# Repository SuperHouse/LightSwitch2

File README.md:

Home Automation Light Switch (2 Button)
========================================
Copyright 2014-2017 SuperHouse Automation Pty Ltd  
SuperHouse site:  <www.superhouse.tv>  

Illuminated push button breakout with an RJ45 socket, for mounting
in a wall panel as part of a home automation system.

Features:

 * 2 Illuminated push buttons
 * RJ45 breakout to allow connecting using Cat-5 cable

More information is available at:

  http://www.superhouse.tv/lightswitch

INSTALLATION
------------
The design is saved as an EAGLE project. EAGLE PCB design software is
available from www.cadsoftusa.com free for non-commercial use. To use
this project download it and place the directory containing these files
into the "eagle" directory on your computer. Then open EAGLE and
navigate to the project.

DISTRIBUTION
------------
The specific terms of distribution of this project are governed by the
license referenced below.

LICENSE
-------
Licensed under the TAPR Open Hardware License (www.tapr.org/OHL).
The "license" folder within this repository also contains a copy of
this license in plain text format.

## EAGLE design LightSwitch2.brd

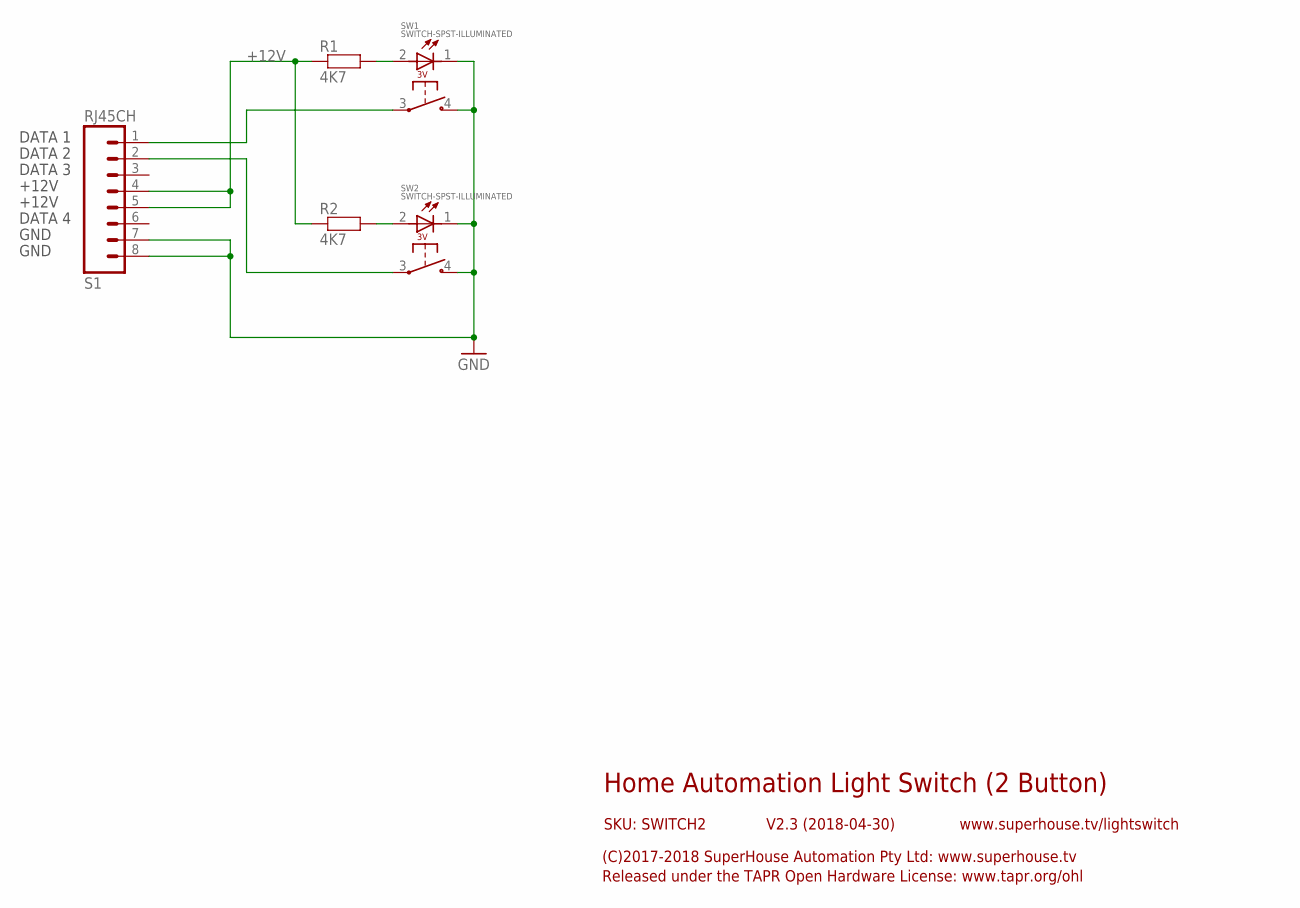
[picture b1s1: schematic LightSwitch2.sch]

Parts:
R1, R2: 4K7; 0603
S1: RJ45CH
SW1, SW2: SWITCH-SPST-ILLUMINATED

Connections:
+12V: R1.1, R2.1, S1.4, S1.5
GND: S1.7, S1.8, SW1.1 (-), SW1.4 (NO), SW2.1 (-), SW2.4 (NO)
unnamed: R1.2, SW1.2 (+)
unnamed: R2.2, SW2.2 (+)
unnamed: S1.1, SW1.3 (COM)
unnamed: S1.2, SW2.3 (COM)

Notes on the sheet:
Home Automation Light Switch (2 Button)
V2.3 (2018-04-30)
SKU: SWITCH2
(C)2017-2018 SuperHouse Automation Pty Ltd: www.superhouse.tv
Released under the TAPR Open Hardware License: www.tapr.org/ohl
www.superhouse.tv/lightswitch
DATA 1
DATA 2
DATA 3
DATA 4
+12V
GND

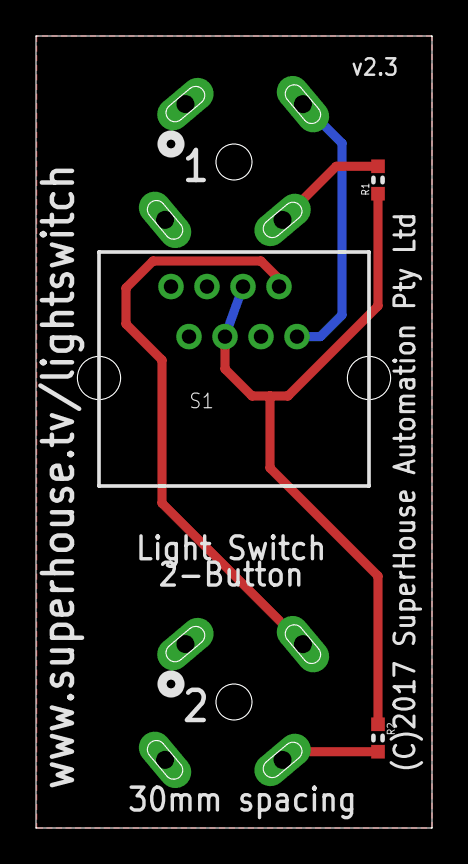
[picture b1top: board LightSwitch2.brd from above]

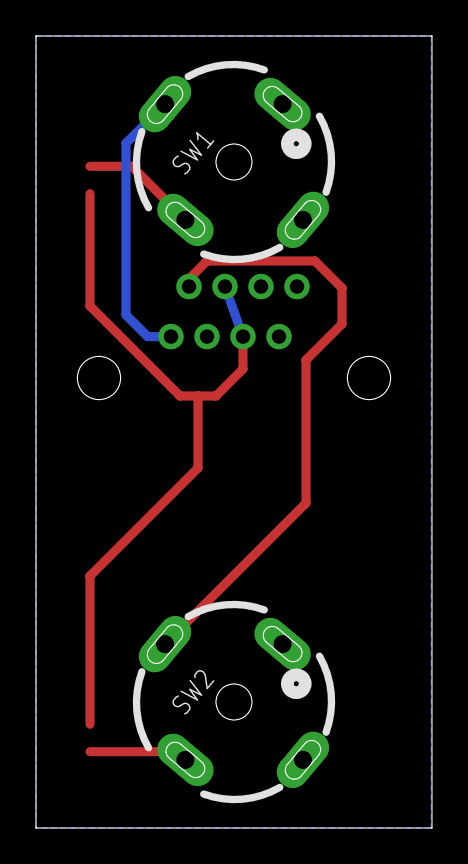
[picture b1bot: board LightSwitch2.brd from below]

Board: 2 copper layers, 22.0 x 44.0 mm, 5 parts (2 on the bottom side), 6 nets.

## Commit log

2017-10-07 Initial project import
2017-10-07 Improved labels for clarity
2017-10-07 Replaced buttons with more common SPST type
2017-10-12 Final tweaks preparing for v2.0 release
2018-04-05 Updated button and RJ45 socket footprints for v2.2
2018-04-30 RJ45 footprint change for v2.3

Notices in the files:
LightSwitch2.brd:
(C)2017 SuperHouse Automation Pty Ltd
